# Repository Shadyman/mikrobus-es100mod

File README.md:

# mikrobus-Compatible Everset ES100-MOD WWVB Receiver
This is a basic board in the _mikroBUS add-on board_ form factor (small) to allow the use of the [ES100-MOD](https://universal-solder.ca/product/everset-es100-mod-wwvb-bpsk-phase-modulation-receiver-module/) module. 

The ES100-MOD contains the Everset ES100 and supporting circuitry on a castellated black PCB. 

The ES100 is used to receive the (phase-modulated) WWVB time signal.

# Mikrobus Pins Used
- VCC
- GND
- SDA
- SCL
- EN  (RESET)
- INT

# Project Status
- [x] Schematic Creation
- [x] PCB Creation
- [ ] Initial PCB Test Run
- [ ] PCB Testing

# References
- [ES100-MOD Item Page - Universal-Solder.ca](https://universal-solder.ca/product/everset-es100-mod-wwvb-bpsk-phase-modulation-receiver-module/)
- [Mikrobus Standard - Mikroelectronica](https://www.mikroe.com/mikrobus)

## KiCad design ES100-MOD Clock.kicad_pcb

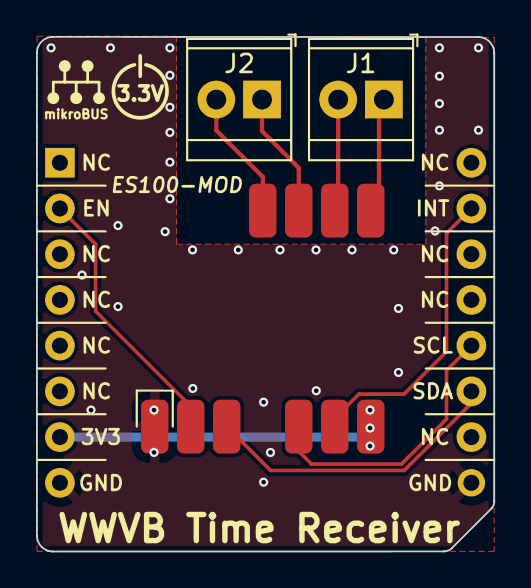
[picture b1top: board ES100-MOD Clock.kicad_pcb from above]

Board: 2 copper layers, 25.4 x 28.6 mm, 4 parts (0 on the bottom side), 10 nets.

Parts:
J1: ANT1; TerminalBlock_TE_282834-2_1x02_P2.54mm_Horizontal
J2: ANT2; TerminalBlock_TE_282834-2_1x02_P2.54mm_Horizontal
J99: mikrobus-add-on; mikrobus-small
U1: ES100-MOD-v1.1; ES100-MOD

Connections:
+3V3: J99.7 (+3.3V), U1.6 (VDD)
/AN1+: J1.2, U1.8 (AN1+)
/AN1-: J1.1, U1.7 (AN1-)
/AN2+: J2.2, U1.10 (AN2+)
/AN2-: J2.1, U1.9 (AN2-)
EN: J99.2 (RST), U1.2 (EN)
GND: J99.8 (GND), J99.16 (GND), U1.1 (GND)
INT: J99.10 (INT), U1.5 (IRQ)
SCL: J99.13 (SCL), U1.4 (SCL)
SDA: J99.14 (SDA), U1.3 (SDA)

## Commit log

2024-02-15 Create LICENSE
2024-02-15 Rename LICENSE to LICENSE.md
2024-02-15 Added PCB footprints by upload
2024-02-15 Schematic Plotter Output

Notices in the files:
ES100-MOD Clock.kicad_pcb:
CC BY-SA 4.0
